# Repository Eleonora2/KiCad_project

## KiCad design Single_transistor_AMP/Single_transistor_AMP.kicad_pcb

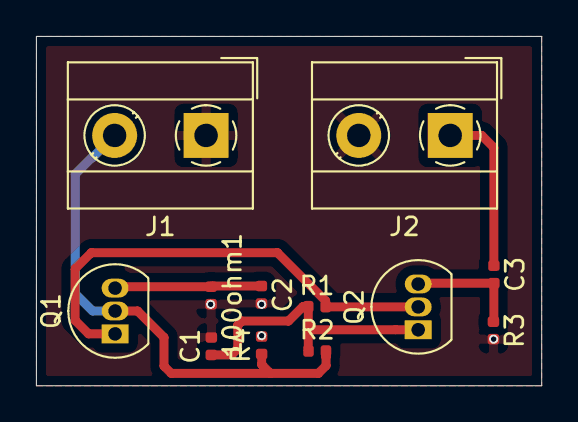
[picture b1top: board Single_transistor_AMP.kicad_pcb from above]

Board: 4 copper layers, 28.1 x 19.4 mm, 12 parts (0 on the bottom side), 7 nets.

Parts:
100ohm1: R5; R_0402_1005Metric
C1, C2, C3: 0,1uF; C_0402_1005Metric
J1, J2: Screw_Terminal_01x02; TerminalBlock_MetzConnect_Type101_RT01602HBWC_1x02_P5.08mm_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
Q1, Q2: 2N2222A; TO-92_Inline
R1, R3: 1kohm; R_0402_1005Metric
R2: 20kohm; R_0402_1005Metric
R4: 3kohm; R_0402_1005Metric

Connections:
+15V: C1.1, Q2.1, R1.1, R2.1
GNDREF: 100ohm1.2, C1.2, C2.2, J1.1, J2.2, R3.2, R4.2
unnamed: 100ohm1.1, C2.1, Q1.3
unnamed: C3.1, J2.1
unnamed: C3.2, Q2.3, R3.1
unnamed: J1.2, Q1.2, R2.2, R4.1
unnamed: Q1.1, Q2.2, R1.2

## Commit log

2020-10-08 1 md pabeigts
2020-11-17 6nod md
2021-01-26 kursa dabs
